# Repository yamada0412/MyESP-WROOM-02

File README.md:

# MyESP-WROOM-02
MyESP-WROOM-02

# これはなに？
ESP-WROOM-02とDHT11を使った温度・湿度ロガーです。

# 製造方法
*_GerberフォルダのファイルをPCB製造業者へ送って製造を依頼します。

# 必要部品一覧

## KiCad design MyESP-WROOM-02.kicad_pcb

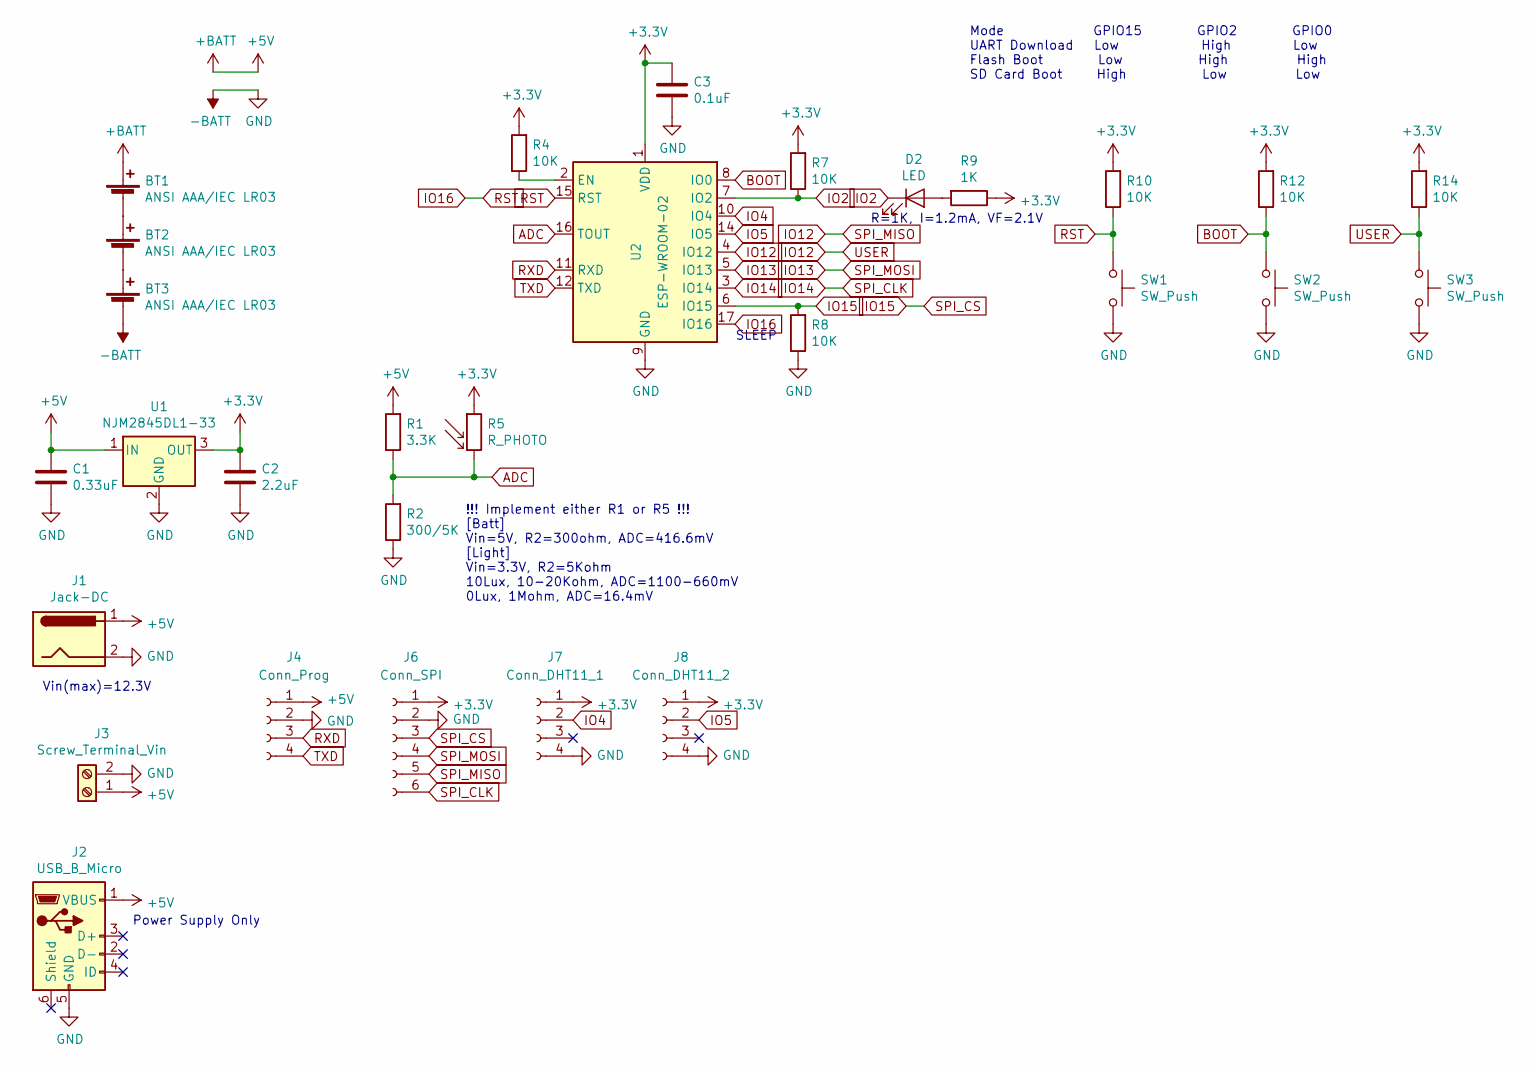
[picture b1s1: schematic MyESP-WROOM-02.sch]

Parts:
BT1, BT2, BT3: ANSI AAA/IEC LR03; BatteryHolder_Keystone_2466_1xAAA
C1: 0.33uF; C_Disc_D5.0mm_W2.5mm_P5.00mm
C2: 2.2uF; C_Disc_D5.0mm_W2.5mm_P5.00mm
C3: 0.1uF; C_Disc_D5.0mm_W2.5mm_P5.00mm
D2: LED; LED_D3.0mm
J1: Jack-DC; BarrelJack_Horizontal
J2: USB_B_Micro; USB_Micro-B_GCT_USB3076-30-A
J3: Screw_Terminal_Vin; TerminalBlock_bornier-2_P5.08mm
J4: Conn_Prog; PinSocket_1x04_P2.54mm_Vertical
J6: Conn_SPI; PinSocket_1x06_P2.54mm_Vertical
J7: Conn_DHT11_1; PinSocket_1x04_P2.54mm_Vertical
J8: Conn_DHT11_2; PinSocket_1x04_P2.54mm_Vertical
R1: 3.3K; R_Axial_DIN0207_L6.3mm_D2.5mm_P10.16mm_Horizontal
R2: 300/5K; R_Axial_DIN0207_L6.3mm_D2.5mm_P10.16mm_Horizontal
R4, R7, R8, R10, R12, R14: 10K; R_Axial_DIN0207_L6.3mm_D2.5mm_P10.16mm_Horizontal
R5: R_PHOTO; LED_D3.0mm
R9: 1K; R_Axial_DIN0207_L6.3mm_D2.5mm_P10.16mm_Horizontal
SW1, SW2, SW3: SW_Push; SW_PUSH_6mm
U1: NJM2845DL1-33; TO-252-2
U2: ESP-WROOM-02

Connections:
+3V3: C2.1, C3.1, J6.1, J7.1, J8.1, R4.2, R5.1, R7.2, R9.1, R10.2, R12.2, R14.2, U1.3 (OUT), U2.1 (VDD)
+5V: BT1.1 (+), C1.1, J1.1, J2.1 (VBUS), J3.1, J4.1, R1.2, U1.1 (IN)
-BATT: BT3.2 (-), C1.2, C2.2, C3.2, J1.2, J2.5 (GND), J3.2, J4.2, J6.2, J7.4, J8.4, R2.1, R8.1, SW1.2, SW2.2, SW3.2, U1.2 (GND), U2.9 (GND), U2.13 (GND), U2.18 (GND), U2.19 (GND)
ADC: R1.1, R2.2, R5.2, U2.16 (TOUT)
BOOT: R12.1, SW2.1, U2.8 (IO0)
IO2: D2.1 (K), R7.1, U2.7 (IO2)
IO4: J7.2, U2.10 (IO4)
IO5: J8.2, U2.14 (IO5)
IO12: J6.5, R14.1, SW3.1, U2.4 (IO12)
IO13: J6.4, U2.5 (IO13)
IO14: J6.6, U2.3 (IO14)
IO15: J6.3, R8.2, U2.6 (IO15)
IO16: R10.1, SW1.1, U2.15 (RST), U2.17 (IO16)
unnamed: BT1.2 (-), BT2.1 (+)
unnamed: BT2.2 (-), BT3.1 (+)
unnamed: D2.2 (A), R9.2
unnamed: R4.1, U2.2 (EN)
RXD: J4.3, U2.11 (RXD)
TXD: J4.4, U2.12 (TXD)

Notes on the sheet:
Vin(max)=12.3V
Mode GPIO15 GPIO2 GPIO0 UART Download Low High Low Flash Boot Low High High SD Card Boot High Low Low
!!! Implement either R1 or R5 !!! [Batt] Vin=5V, R2=300ohm, ADC=416.6mV [Light] Vin=3.3V, R2=5Kohm 10Lux, 10-20Kohm, ADC=1100-660mV 0Lux, 1Mohm, ADC=16.4mV
SLEEP
Power Supply Only
R=1K, I=1.2mA, VF=2.1V

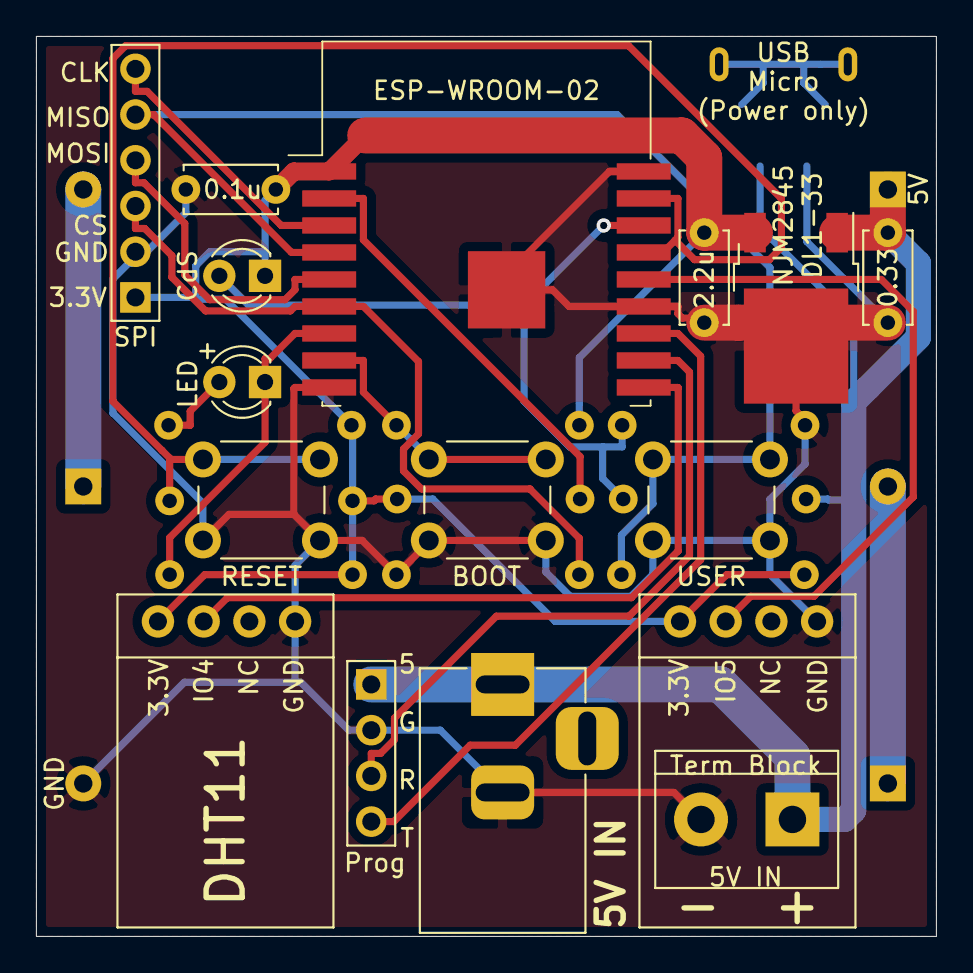
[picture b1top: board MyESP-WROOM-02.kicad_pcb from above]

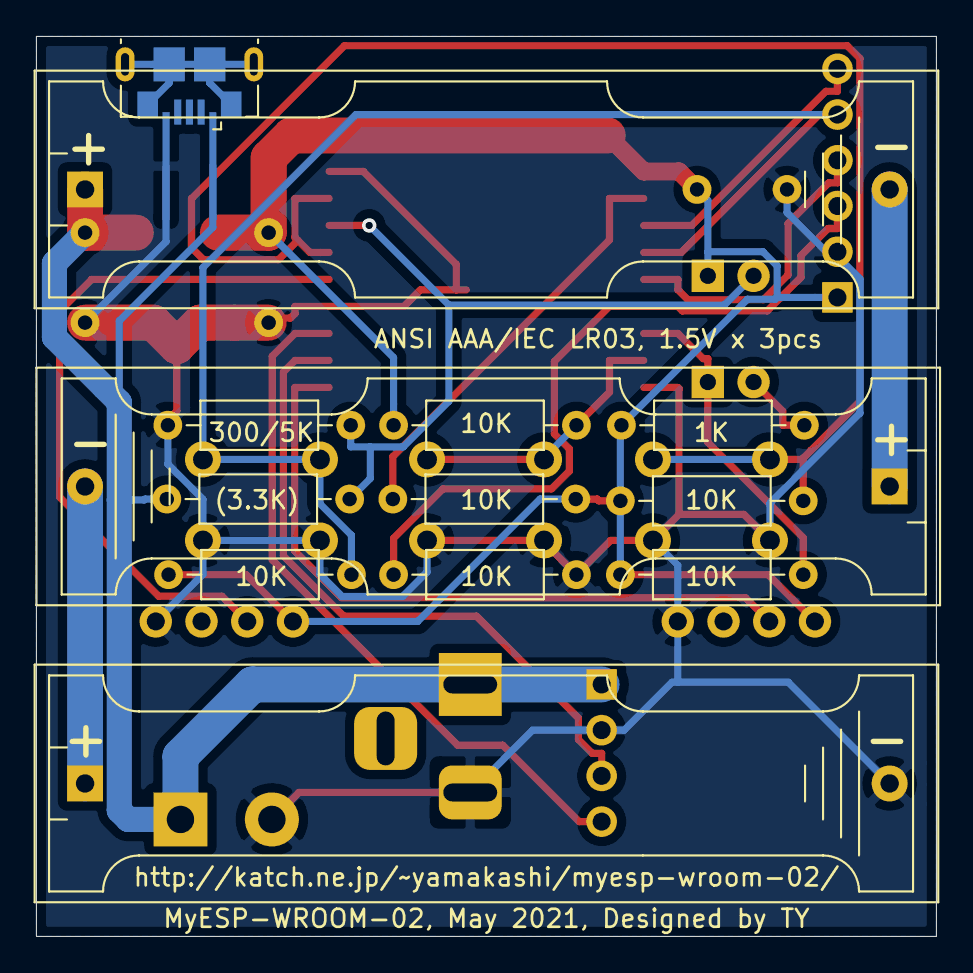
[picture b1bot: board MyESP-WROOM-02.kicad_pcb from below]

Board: 2 copper layers, 50.0 x 50.0 mm, 29 parts (13 on the bottom side), 19 nets.

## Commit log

2021-06-13 initial
    initial
